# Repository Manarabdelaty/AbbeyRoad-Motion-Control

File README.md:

# AbbeyRoad Motion Control

The motion control unit interacts with an ebike controller to control brushless dc motor rotation speed and direction.

### Hardware Components

The contorl circuit contains the following hardwarer componets:

- STM32 Blue pill 
- Two  Digital to Analog Converters [DAC](https://www.sunfounder.com/learn/Sensor-Kit-v2-0-for-Arduino/lesson-33-analog-digital-converter-sensor-kit-v2-0-for-arduino.html)
- [4 channel relay board](https://www.electrodragon.com/product/4-channels-relay-module/) 
- HC-05 Bluetooth module 
- Two Bidirectional Level Shifter
- Two Schmitt Inverters
The control circuit lay

### Circuit Schematic & Layout

The pcb design files are avaialble at [PCB](https://github.com/Manarabdelaty/AbbeyRoad-Motion-Control/tree/master/PCB)

The hardware componet's connectin are shown below: 

The circuit layout is show below:

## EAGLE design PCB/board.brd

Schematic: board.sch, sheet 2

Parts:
BLUETOOTH: MA04-1
C2, C3: 10uf; E3,5-8
IC1, IC2: 74HC14N; DIL14
R2, R3: 1k; 0207/12
RELAY: MA06-1
SV1, SV3: MA10-1
SV2: MA12-1
SV4: MA03-1
U$1, U$2: SHIFT
U$3: BLUE_PILL
U$5, U$6: DAC

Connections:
3.3V: U$1.3.3V, U$2.3.3V, U$3.P$23 (3.3V)
5V: IC1.14 (VCC), IC2.14 (VCC)
GND: BLUETOOTH.2, C2.-, C3.-, IC1.7 (GND), IC2.7 (GND), RELAY.2, SV3.1, SV3.2, SV3.3, SV3.4, SV3.5, SV3.6, SV3.7, SV3.8, SV3.9, SV3.10, U$1.-, U$1.GND, U$2.-, U$2.GND, U$3.P$19 (GND2), U$5.GND, U$6.GND
GND1: U$3.P$21 (GND1)
IN1: RELAY.3, U$3.P$29 (PA7)
IN2: RELAY.4, U$3.P$30 (PA6)
IN3: RELAY.5, U$3.P$31 (PA5)
IN4: RELAY.6, U$3.P$35 (PA1)
INPUTFROMSENSOR: SV4.3, U$2.HV2
INPUTFROMSENSOR2: SV4.2, U$1.HV2
INV_1: IC1.12 (O), U$3.P$28 (PB0)
INV_2: IC2.12 (O), U$3.P$27 (PB1)
unnamed: R3.2, U$1.LV2
unnamed: R2.2, U$2.LV2
unnamed: C3.+, IC1.13 (I), R2.1
unnamed: C2.+, IC2.13 (I), R3.1
PA8: SV2.10, U$3.P$5 (PA8)
PB13: SV2.7, U$3.P$2 (PB13)
PB14: SV2.8, U$3.P$3 (PB14)
PB15: SV2.9, U$3.P$4 (PB15)
RX: SV2.12, U$3.P$7 (PA10)
SCL_1: U$3.P$14 (PB6), U$5.SCL
SCL_2: U$3.P$26 (PB10), U$6.SCL
SDA_1: U$3.P$15 (PB7), U$5.SDA
SDA_2: U$3.P$25 (PB11), U$6.SDA
SENSORINPUT: SV2.2, U$3.P$8 (PA11)
SENSORINPUT2: SV2.1, U$3.P$9 (PA12)
SPEEDOUT: SV2.6, U$5.AOUT
SPEEDOUT2: SV2.5, U$6.AOUT
TX: BLUETOOTH.3, SV2.11, U$3.P$6 (PA9), U$3.P$33 (PA3)
VCC: BLUETOOTH.1, RELAY.1, SV1.1, SV1.2, SV1.3, SV1.4, SV1.5, SV1.6, SV1.7, SV1.8, SV1.9, SV1.10, U$1.5V, U$2.5V, U$3.P$18 (5V)
VREF: SV2.4, U$5.VCC
VREF2: SV2.3, U$6.VCC

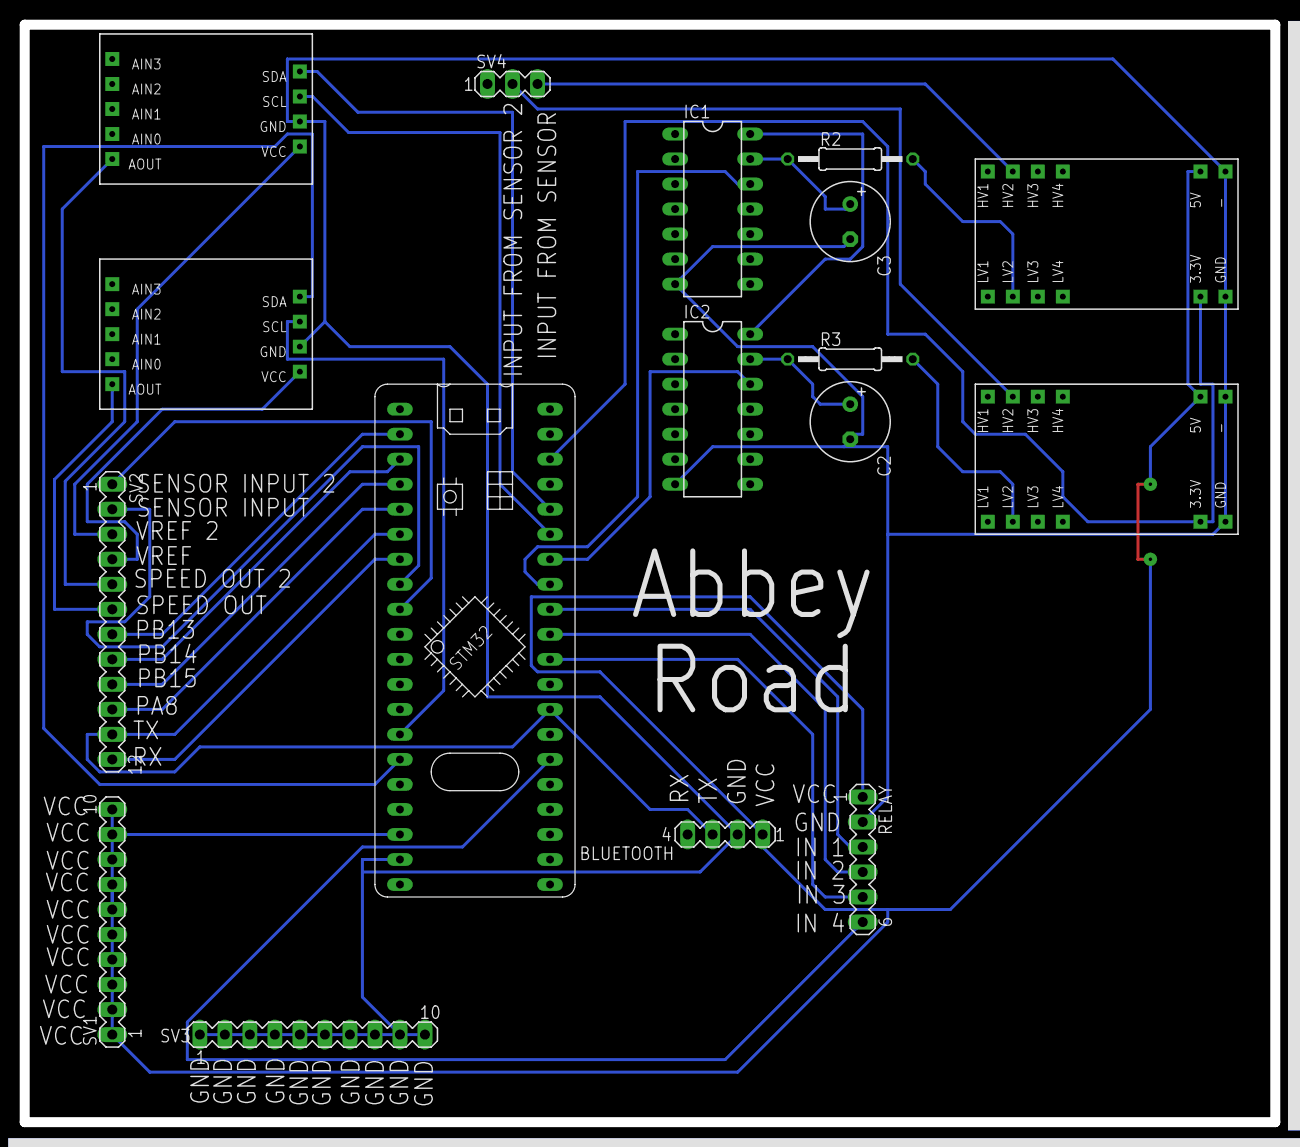
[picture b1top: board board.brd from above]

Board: 2 copper layers, 127.0 x 111.4 mm, 17 parts (0 on the bottom side), 32 nets.

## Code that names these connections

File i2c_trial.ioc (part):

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Mcu.Name=STM32F103C(8-B)Tx
Mcu.Package=LQFP48
Mcu.UserName=STM32F103C8Tx
PA1.Signal=GPIO_Output
PA10.Mode=Asynchronous
PA10.Signal=USART1_RX
PA13.Mode=Serial_Wire
PA13.Signal=SYS_JTMS-SWDIO
PA14.Mode=Serial_Wire
PA14.Signal=SYS_JTCK-SWCLK
PA2.Mode=Asynchronous
PA2.Signal=USART2_TX
PA3.Mode=Asynchronous
PA3.Signal=USART2_RX
PA5.Signal=GPIO_Output
PA6.Signal=GPIO_Output
PA7.Signal=GPIO_Output
PA9.Mode=Asynchronous
PA9.Signal=USART1_TX
PB0.GPIOParameters=GPIO_PuPd,GPIO_ModeDefaultEXTI
PB0.GPIO_ModeDefaultEXTI=GPIO_MODE_IT_RISING
PB0.GPIO_PuPd=GPIO_PULLDOWN
PB0.Signal=GPXTI0
PB1.GPIOParameters=GPIO_PuPd,GPIO_ModeDefaultEXTI
PB1.GPIO_ModeDefaultEXTI=GPIO_MODE_IT_RISING
PB1.GPIO_PuPd=GPIO_PULLDOWN
PB1.Signal=GPXTI1
PB10.Mode=I2C
PB10.Signal=I2C2_SCL
PB11.Mode=I2C
PB11.Signal=I2C2_SDA
PB6.Mode=I2C
PB6.Signal=I2C1_SCL
PB7.Mode=I2C
PB7.Signal=I2C1_SDA
PD0-OSC_IN.Mode=HSE-External-Oscillator
PD0-OSC_IN.Signal=RCC_OSC_IN
PD1-OSC_OUT.Mode=HSE-External-Oscillator
PD1-OSC_OUT.Signal=RCC_OSC_OUT
RCC.SYSCLKFreq_VALUE=72000000
RCC.SYSCLKSource=RCC_SYSCLKSOURCE_PLLCLK
board=custom

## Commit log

2019-12-15 final
2019-12-15 added pcb
